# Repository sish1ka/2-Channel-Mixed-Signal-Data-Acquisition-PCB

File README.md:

# 2-Channel-Mixed-Signal-Data-Acquisition-PCB

## Overview

This project involves the design of a 2-channel mixed-signal data acquisition system intended to measure 0–5 V analog signals and convert them into digital data for microcontroller-based processing and analysis.

Each analog input passes through input protection, voltage scaling, buffering, and active low-pass filtering before being sampled by a 12-bit ADC on an STM32 microcontroller.

The system is being designed and simulated using LTspice and will be implemented as a 2-layer PCB using KiCad. In the future, Embedded C will be used for microcontroller data acquisition and MATLAB will be used for data analysis.

## Objectives

* Design a 2-channel analog data acquisition system
* Accept 0–5 V analog input signals
* Scale the input signals to an ADC-compatible voltage range
* Implement input protection against abnormal voltage excursions
* Buffer the analog signals to minimize loading between circuit stages
* Implement 2nd-order active low-pass filtering
* Sample the conditioned signals using a 12-bit ADC
* Transfer acquired data through UART
* Verify circuit behavior through simulation
* Design and verify a 2-layer PCB
* Analyze acquired data using MATLAB

## Tools

* LTspice
* KiCad
* C
* MATLAB
* Git / GitHub

## Circuit Design

## Design Summary

| Parameter                 |                Value |
| ------------------------- | -------------------: |
| Number of channels        |                    2 |
| Input signal              |                0–5 V |
| ADC voltage range         |              0–3.3 V |
| ADC resolution            |               12-bit |
| Sampling rate             |       4 kS/s/channel |
| Useful bandwidth          |             0–100 Hz |
| Low-pass filter           | 2nd-order Sallen-Key |
| Filter cutoff             |              ~297 Hz |
| Nominal system gain       |            ~0.60 V/V |
| Maximum nominal ADC input |               ~3.0 V |
| Microcontroller           |        STM32G031K8T6 |
| Analog op-amp             |              MCP6004 |
| PCB layers                |                    2 |
| PCB dimensions            |          ~80 × 50 mm |
| UART baud rate            |          460800 baud |z

## LTspice Simulation

### Verification Procedure

The analog front end is being verified using a node-by-node transient analysis.

Each verification step checks a specific electrical condition before proceeding to the next stage.

### 1. Voltage divider

**Purpose:**
Verify that the input protection resistor and voltage divider produce the expected scaled voltage for a 0–5 V input signal.

**Circuit Configuration:**

| Component                 |   Value |
| ------------------------- | ------: |
| Input protection resistor |    1 kΩ |
| R_TOP                     | 16.5 kΩ |
| R_BOTTOM                  |   10 kΩ |

**Test Signal:**

```text
SINE(2.5 2.5 10)
```

The input signal has a 2.5 V DC offset, 2.5 V amplitude, and 10 Hz frequency, resulting in a 0–5 V input waveform.

**Transient Analysis:**

```text
.tran 100m
```

The 100 ms simulation window corresponds to one complete cycle of the 10 Hz input signal.

**Procedure:**

1. Apply the 0–5 V test signal to the input.
2. Run a transient analysis for 100 ms in LTspice.
3. Probe the input node.
4. Confirm that the input signal ranges from 0 V to 5 V.
5. Probe the output of the voltage divider.
6. Confirm that the scaled signal ranges from approximately 0 V to 1.82 V.

**Expected Result:**

| Parameter             | Expected |
| --------------------- | -------: |
| Input minimum         |      0 V |
| Input maximum         |      5 V |
| Scaled output minimum |     ~0 V |
| Scaled output maximum |  ~1.82 V |

**Measured Result:**
`Vin = 0–5.00 V`
`Vscaled = 0–1.82 V`

**Result:** Pass

### 2. Diode Voltage Protection Verification

**Purpose:**
Verify that the protection diode limits abnormal negative voltage excursions at the scaled node.

A bipolar test signal is applied to intentionally drive the input below the normal 0–5 V operating range.

**Test Signal:**

```text
SINE(0 5 10)
```

This produces a −5 V to +5 V input waveform.

**Procedure:**

1. Apply the bipolar test signal to the input.
2. Run a transient analysis for 100 ms in LTspice.
3. Probe the scaled node.
4. Observe the negative voltage excursion without the protection diode.
5. Enable the protection diode.
6. Repeat the simulation.
7. Compare the negative voltage excursion with and without the diode.

**Expected Result:**

The protection diode should conduct during the negative voltage excursion and limit the negative voltage at the protected node.

**Measured Result:**
Without the diode, the scaled node follows the negative input excursion. With the diode connected, the negative voltage is clamped and the scaled node no longer follows the negative excursion below the diode's forward-voltage region.

**Result:** Pass

### 3. Buffer Verification

**Purpose:**
Verify that the voltage buffer reproduces the scaled input signal without significantly changing its voltage level. The buffer also isolates the voltage divider from the following filter stage by providing high input impedance and low output impedance.

**Buffer Configuration:**

| Parameter      |                                        Value |
| -------------- | -------------------------------------------: |
| Op-Amp         |                              UniversalOpamp2 |
| Configuration  |                             Voltage follower |
| Supply voltage |                                  3.3 V / 0 V |
| Buffer input   |                       Voltage divider output |
| Buffer output  |                                 Filter input |
| Feedback       | Output directly connected to inverting input |

**Procedure:**

1. Apply the 0–5 V input signal using `SINE(2.5 2.5 10)`.
2. Run the transient simulation for 100 ms.
3. Measure the voltage at the output of the voltage divider.
4. Measure the voltage at the output of the buffer.
5. Compare the two waveforms over the full input cycle.

**Expected Result:**

The buffer output should closely follow the voltage-divider output with approximately unity voltage gain.

$$
A_v = \frac{V_{OUT}}{V_{IN}} \approx 1
$$

For the 0–5 V input signal, the voltage divider produces approximately 0–1.82 V. Therefore, the buffer output should also be approximately 0–1.82 V.

| Measurement           | Expected Result |
| --------------------- | --------------: |
| Buffer input minimum  |            ~0 V |
| Buffer input maximum  |         ~1.82 V |
| Buffer output minimum |            ~0 V |
| Buffer output maximum |         ~1.82 V |
| Voltage gain          |          ~1 V/V |

**Measured Result:**

The buffer output closely follows the voltage-divider output. The buffer input and output waveforms overlap over the 0–1.82 V range, confirming that the voltage follower provides approximately unity gain without significantly altering the signal amplitude.

**Result:** Pass

### 4. Sallen-Key Filter Response Verification

**Purpose:**
Verify that the Sallen-Key stage provides the intended second-order low-pass response, including the expected low-frequency gain, cutoff frequency, and roll-off behavior.

**Filter Configuration:**

| Parameter     |       Value |
| ------------- | ----------: |
| R1            |     5.36 kΩ |
| R2            |     5.36 kΩ |
| C1            |      100 nF |
| C2            |      100 nF |
| Rf            |     5.90 kΩ |
| Rg            |       10 kΩ |
| Op-Amp Supply | 3.3 V / GND |

**Theoretical Low-Pass Cutoff:**

For equal resistor and capacitor values:

$$
f_c = \frac{1}{2\pi RC}
$$

$$
f_c = \frac{1}{2\pi(5.36\,k\Omega)(100\,nF)}
\approx 297\,Hz
$$

The Sallen-Key gain is:

$$
K = 1 + \frac{R_f}{R_g}
$$

$$
K = 1 + \frac{5.90\,k\Omega}{10\,k\Omega}
\approx 1.59
$$

The corresponding low-frequency magnitude is:

$$
20\log_{10}(1.59) \approx 4.03\,dB
$$

For a second-order low-pass filter, the cutoff frequency is approximately **3 dB below the passband magnitude**. Therefore, with a passband magnitude of approximately +4 dB, the expected magnitude at the cutoff is approximately +1 dB.

**Procedure:**

1. Set the LTspice input source to:

   * DC value: `2.5 V`
   * AC amplitude: `1 V`
   * AC phase: `0°`
2. Run an AC sweep using:
   `.ac dec 100 1 100k`
3. Plot the filter transfer function:
   `V(FILTER_OUT)/V(BUF_OUT)`
4. Measure the magnitude in the low-frequency passband.
5. Measure the magnitude near the theoretical cutoff frequency of 297 Hz.
6. Verify the expected attenuation beyond the cutoff region.

**Expected Result:**

| Measurement             |       Expected |
| ----------------------- | -------------: |
| Low-frequency gain      |      ~1.59 V/V |
| Low-frequency magnitude |      ~+4.03 dB |
| Cutoff frequency        |        ~297 Hz |
| Magnitude at cutoff     |      ~+1.03 dB |
| High-frequency roll-off | ~−40 dB/decade |

**Measured Result:**

* At **10 Hz:** approximately **+4 dB**
* At **297 Hz:** approximately **+1 dB**
* The measured response is consistent with the expected second-order low-pass behavior.

**Result:** Pass

The measured passband gain and attenuation at 297 Hz closely match the theoretical response. The filter therefore provides the intended low-pass behavior with a cutoff frequency of approximately 297 Hz.

### 5. ADC Input Range Verification

**Purpose:**
Verify that the conditioned analog signal remains within the STM32 ADC input range and that the complete analog front end provides the intended voltage scaling.

**ADC Configuration:**

| Parameter                    |       Value |
| ---------------------------- | ----------: |
| ADC voltage range            |     0–3.3 V |
| ADC resolution               |      12-bit |
| Input signal                 |       0–5 V |
| ADC input filter             | 47 Ω + 1 nF |
| Expected maximum ADC voltage |      ~3.0 V |

**Procedure:**

1. Connect the Sallen-Key filter output to the ADC input through the 47 Ω series resistor.
2. Add a 1 nF capacitor from the ADC input node to GND.
3. Apply a 0–5 V sinusoidal input using:
   `SINE(2.5 2.5 10)`
4. Run a transient simulation using:
   `.tran 100m`
5. Plot the ADC input node voltage, `V(ADC_IN)`.
6. Verify that the ADC input remains within the 0–3.3 V operating range.

**Expected Result:**

For a 5 V maximum input, the nominal analog gain of approximately 0.60 V/V gives:

$$
V_{ADC,max} \approx 5V \times 0.60
$$

$$
V_{ADC,max} \approx 3.0V
$$

The ADC input should therefore remain below the 3.3 V supply while utilizing most of the available ADC range.

**Measured Result:**

The simulated ADC input waveform remained sinusoidal and reached approximately **2.9 V maximum** for a 5 V maximum input.

| Measurement          | Result |
| -------------------- | -----: |
| Input minimum        |   ~0 V |
| Input maximum        |    5 V |
| ADC minimum          |   ~0 V |
| ADC maximum          | ~2.9 V |
| ADC supply/reference |  3.3 V |

The maximum ADC voltage is approximately 0.4 V below the 3.3 V supply, providing headroom while maintaining a large usable portion of the ADC input range.

**Result:** Pass

The simulated ADC input remains within the 0–3.3 V range and is suitable for connection to the STM32 ADC.

### Results

| Verification                | Theoretical                | Measured                   | Error | Result |
| --------------------------- | -------------------------- | -------------------------- | ----: | ------ |
| Voltage scaling             | 0–1.89 V                   | 0–1.89 V                   |     — | Pass   |
| Negative voltage protection | Negative excursion clamped | Negative excursion clamped |     — | Pass   |
| Buffer                      | Unity gain                 | Unity gain                 |     — | Pass   |
| Filter cutoff               | ~297 Hz                    | ~297 Hz                    |     — | Pass   |
| Complete analog chain       | 0–3.0 V ADC input          | 0–2.9 V ADC input          | ~3.3% | Pass   |

## PCB Design

The PCB was designed in KiCad based on the verified analog front-end and data acquisition circuit.

The board integrates two analog signal-conditioning channels with input protection, voltage scaling, signal conditioning, filtering, and a STM32G031K8Tx microcontroller interface.

### PCB Layout

* **Board size:** 80 × 50 mm
* **Design software:** KiCad
* **Layers:** 2-layer PCB
* **Analog channels:** 2
* **Main controller:** STM32G031K8Tx
* **Analog front-end:** MCP6004 quad op-amp
* **Mounting:** Through-hole and surface-mount components
* **Design verification:** Electrical Rules Check (ERC) and Design Rules Check (DRC)
* **Manufacturing outputs:** Gerber files and drill files generated from the final PCB layout

### Components

| Ref.                   | Component         |         Value | Qty. | Footprint                                                        |
| ---------------------- | ----------------- | ------------: | ---: | ---------------------------------------------------------------- |
| C1, C2, C4, C5, C7, C8 | Ceramic Capacitor |        100 nF |    6 | `Capacitor_SMD:C_0805_2012Metric`                                |
| C3, C6                 | Ceramic Capacitor |          1 nF |    2 | `Capacitor_SMD:C_0805_2012Metric`                                |
| D1, D2                 | Diode             |             — |    2 | `Diode_SMD:D_SOD-123`                                            |
| J1, J2                 | 2-Pin Header      |             — |    2 | `Connector_PinHeader_2.54mm:PinHeader_1x02_P2.54mm_Vertical`     |
| J3                     | 5-Pin Header      |             — |    1 | `Connector_PinHeader_2.54mm:PinHeader_1x05_P2.54mm_Vertical`     |
| J4                     | 4-Pin Header      |             — |    1 | `Connector_PinHeader_2.54mm:PinHeader_1x04_P2.54mm_Vertical`     |
| R1, R7                 | Resistor          |          1 kΩ |    2 | `Resistor_THT:R_Axial_DIN0207_L6.3mm_D2.5mm_P10.16mm_Horizontal` |
| R2, R8                 | Resistor          |     16.455 kΩ |    2 | `Resistor_THT:R_Axial_DIN0207_L6.3mm_D2.5mm_P10.16mm_Horizontal` |
| R3, R9, R13, Rg1, Rg2  | Resistor          |         10 kΩ |    5 | `Resistor_THT:R_Axial_DIN0207_L6.3mm_D2.5mm_P10.16mm_Horizontal` |
| R4, R5, R10, R11       | Resistor          |       5.36 kΩ |    4 | `Resistor_THT:R_Axial_DIN0207_L6.3mm_D2.5mm_P10.16mm_Horizontal` |
| R6, R12                | Resistor          |          47 Ω |    2 | `Resistor_THT:R_Axial_DIN0207_L6.3mm_D2.5mm_P10.16mm_Horizontal` |
| Rf1, Rf2               | Resistor          |        5.9 kΩ |    2 | `Resistor_THT:R_Axial_DIN0207_L6.3mm_D2.5mm_P10.16mm_Horizontal` |
| SW1                    | Push Button       |             — |    1 | `Button_Switch_THT:SW_NKK_GW12LJP`                               |
| U1                     | Quad Op-Amp       |       MCP6004 |    1 | `Package_DIP:DIP-14_W7.62mm`                                     |
| U2                     | Microcontroller   | STM32G031K8Tx |    1 | `Package_QFP:LQFP-32_7x7mm_P0.8mm`                               |

**Total components:** 40

### Connector Pinout

Connector pin assignments are defined in the KiCad schematic.

| Connector | Pins | Function                           |
| --------- | ---: | ---------------------------------- |
| J1        |  1–2 | Channel 1 interface                |
| J2        |  1–2 | Channel 2 interface                |
| J3        |  1–5 | Microcontroller / system interface |
| J4        |  1–4 | Power / system interface           |

> **Note:** Refer to the KiCad schematic for the complete electrical pin assignments and net names.

### Power

The board does not include an onboard voltage regulator. The 3.3 V
rail (STM32 VDD/VDDA, MCP6004 V+) is supplied externally through
**J4 pin 1**, which is expected to be driven directly from a
regulated 3.3 V source — for example, the 3.3 V pin available on
many common USB-to-UART adapters (FTDI FT232RL, CP2102, etc.), or a
bench supply. This was a deliberate simplification to reduce
component count on a first custom board; a future revision could
add an onboard LDO (e.g. AMS1117-3.3) to accept a single unregulated
5 V input instead.

### Circuit Parameters

| Parameter        |                Value |
| ---------------- | -------------------: |
| Supply Voltage   |               +3.3 V |
| Input Range      |                0–5 V |
| ADC Range        |              0–3.3 V |
| Sampling Rate    |       4 kS/s/channel |
| Filter           | 2nd-order Sallen-Key |
| Cutoff Frequency |              ~297 Hz |

### KiCAD schematic

### PCB Layout

### 3D View

### Fabrication Outputs

Gerber and drill files are generated using KiCad for PCB manufacturing.

The fabrication outputs include:

* Front and back copper
* Front and back solder mask
* Silkscreen
* Board outline
* Drill files

The generated files are available in `KiCad/Gerbers/`.

### PCB Design Verification

The PCB layout is checked using KiCad's Design Rules Checker (DRC).

**Target:**

* DRC errors: 0
* Unconnected items: 0
* Board outline: ~80 × 50 mm

## Firmware

**Status:** written and compiles cleanly against the STM32G0 HAL;
not flashed or tested on hardware (see Project Status above).

The firmware implements:

* Clock configuration: HSI16 + PLL → 64 MHz HCLK
* ADC1: 2 channels (PA0/PA1), 12-bit, scan mode
* TIM3: configured to trigger ADC conversions at 4 kHz
* DMA: circular-mode capture into a 256-sample ring buffer
  (128 channel-pairs), with half/full-transfer callbacks
* USART1: 460800 baud, TX via DMA
* A 9-byte binary frame protocol — sync bytes, sequence number,
  CH1/CH2 12-bit ADC codes, and an XOR checksum — for streaming
  samples to a host PC

## MATLAB Data Analysis

**Status:** written and tested (via GNU Octave) using synthetic data
matching the firmware's binary protocol; not yet run against real
captured hardware data.

* `filter_analysis.m` — computes the theoretical Sallen-Key frequency
  response directly from component values and can overlay an
  LTspice AC-sweep export for comparison. Runs standalone, no
  hardware needed.

## Future Work

If this project is picked back up:

1. Fabricate the PCB (JLCPCB/PCBWay, ~80×50mm 2-layer) and obtain an
   ST-Link programmer
2. Flash the firmware and verify each stage in isolation (GPIO →
   ADC polling → timer trigger → DMA → UART), per the staged
   bring-up plan this project was designed around
3. Fill in the DC accuracy, frequency-response, and noise
   measurement tables with real values, and compare against the
   LTspice/theoretical predictions already established
4. Consider adding an onboard 3.3 V LDO so the board accepts a
   single unregulated 5 V input

## Files

* `Documentation/` — design images and verification results
* `KiCad/` — schematic and PCB design files
* `LTspice/` — circuit simulations
* `Firmware/` — STM32 firmware
* `MATLAB/` — data analysis scripts
* `BOM/` — bill of materials
* `Gerbers/` — manufacturing outputs

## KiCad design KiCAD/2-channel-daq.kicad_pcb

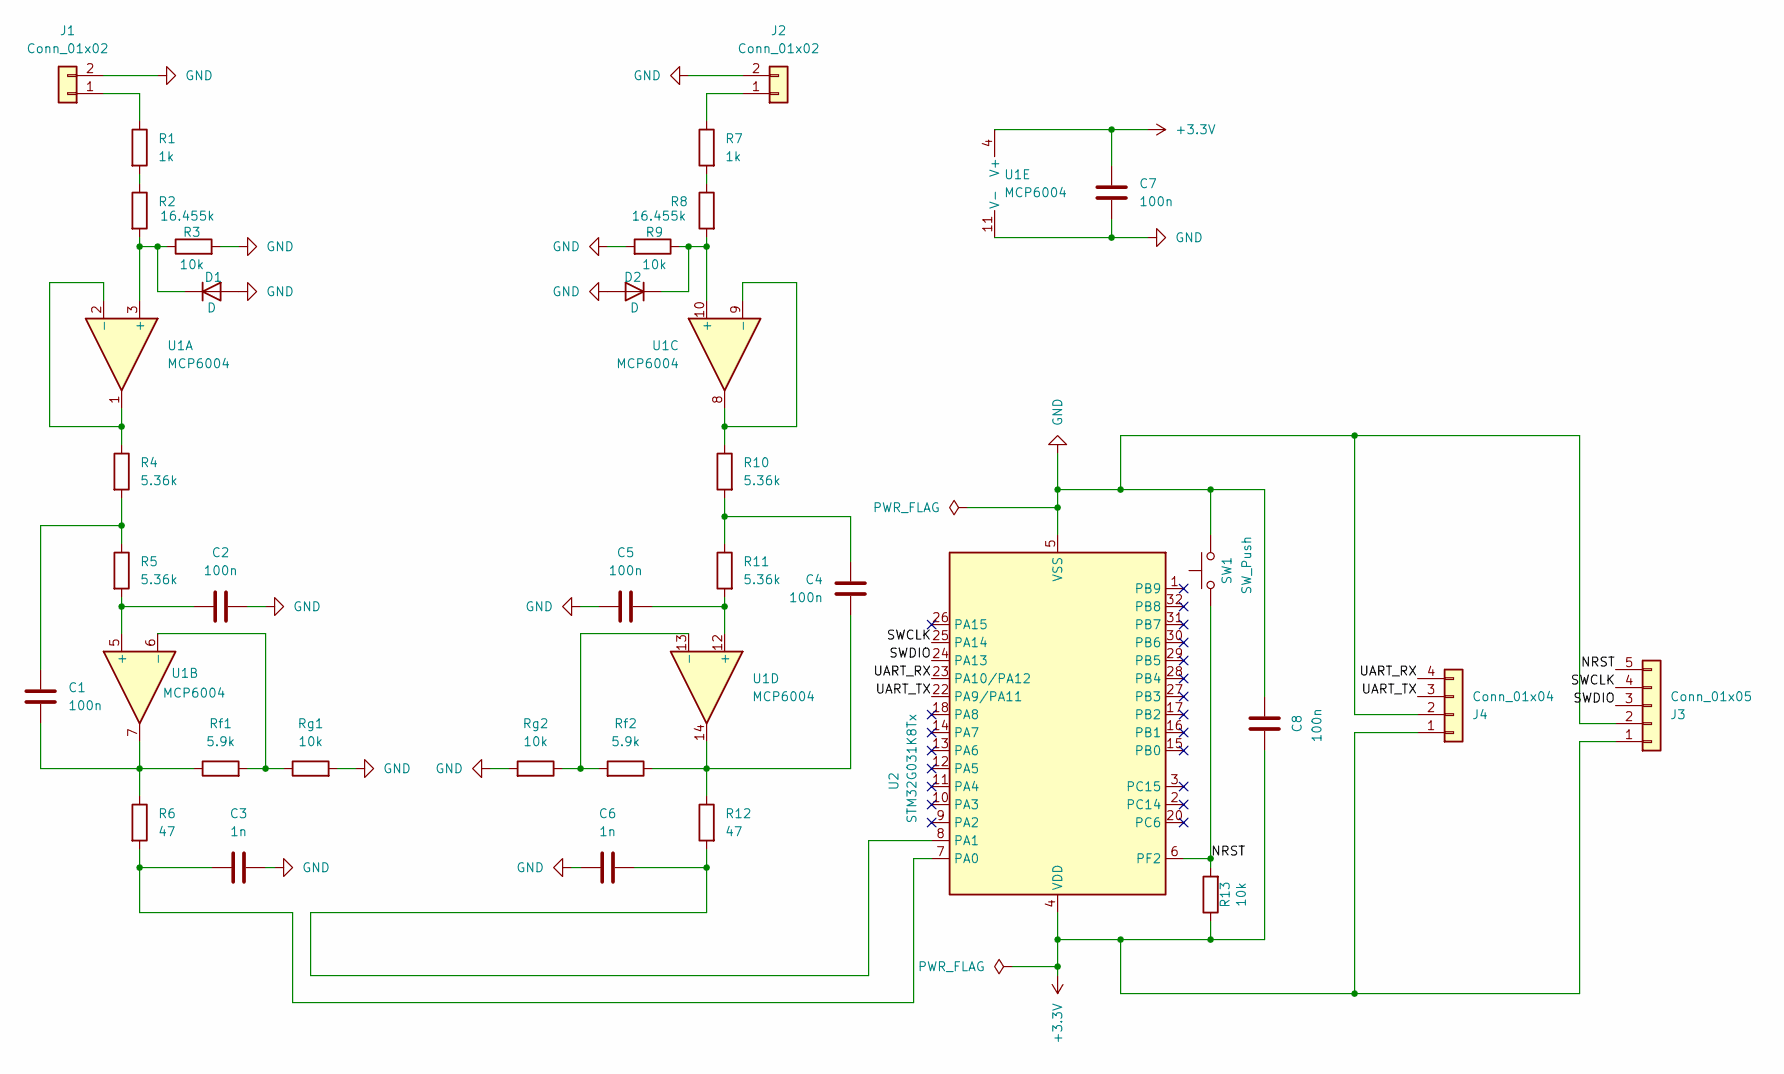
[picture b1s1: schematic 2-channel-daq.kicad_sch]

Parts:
C1, C2, C4, C5, C7, C8: 100n; C_0805_2012Metric
C3, C6: 1n; C_0805_2012Metric
D1, D2: D; D_SOD-123
J1, J2: Conn_01x02; PinHeader_1x02_P2.54mm_Vertical
J3: Conn_01x05; PinHeader_1x05_P2.54mm_Vertical
J4: Conn_01x04; PinHeader_1x04_P2.54mm_Vertical
R1, R7: 1k; R_Axial_DIN0207_L6.3mm_D2.5mm_P10.16mm_Horizontal
R2, R8: 16.455k; R_Axial_DIN0207_L6.3mm_D2.5mm_P10.16mm_Horizontal
R3, R9, R13: 10k; R_Axial_DIN0207_L6.3mm_D2.5mm_P10.16mm_Horizontal
R4, R5, R10, R11: 5.36k; R_Axial_DIN0207_L6.3mm_D2.5mm_P10.16mm_Horizontal
R6, R12: 47; R_Axial_DIN0207_L6.3mm_D2.5mm_P10.16mm_Horizontal
Rf1, Rf2: 5.9k; R_Axial_DIN0207_L6.3mm_D2.5mm_P10.16mm_Horizontal
Rg1, Rg2: 10k; R_Axial_DIN0207_L6.3mm_D2.5mm_P10.16mm_Horizontal
SW1: SW_Push; SW_NKK_GW12LJP
U1: MCP6004; DIP-14_W7.62mm
U2: STM32G031K8Tx; LQFP-32_7x7mm_P0.8mm

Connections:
+3.3V: C7.2, C8.1, J3.1, J4.1, R13.1, U1.4 (V+), U2.4 (VDD)
/NRST: J3.5, R13.2, SW1.1, U2.6 (PF2)
/SWCLK: J3.4, U2.25 (PA14)
/SWDIO: J3.3, U2.24 (PA13)
/UART_RX: J4.4, U2.23 (PA10/PA12)
/UART_TX: J4.3, U2.22 (PA9/PA11)
GND: C2.2, C3.2, C5.2, C6.2, C7.1, C8.2, D1.2 (A), D2.2 (A), J1.2, J2.2, J3.2, J4.2, R3.2, R9.2, Rg1.2, Rg2.2, SW1.2, U1.11 (V-), U2.5 (VSS)
unnamed: C1.1, R4.2, R5.1
unnamed: C1.2, R6.1, Rf1.1, U1.7
unnamed: C4.1, R10.2, R11.1
unnamed: C4.2, R12.1, Rf2.1, U1.14
unnamed: D1.1 (K), R2.2, R3.1, U1.3 (+)
unnamed: D2.1 (K), R8.2, R9.1, U1.10 (+)
unnamed: J1.1, R1.1
unnamed: J2.1, R7.1
unnamed: R1.2, R2.1
unnamed: R7.2, R8.1
unnamed: R4.1, U1.1, U1.2 (-)
unnamed: C2.1, R5.2, U1.5 (+)
unnamed: Rf1.2, Rg1.1, U1.6 (-)
unnamed: R10.1, U1.8, U1.9 (-)
unnamed: C5.1, R11.2, U1.12 (+)
unnamed: Rf2.2, Rg2.1, U1.13 (-)
unnamed: C3.1, R6.2, U2.7 (PA0)
unnamed: C6.1, R12.2, U2.8 (PA1)

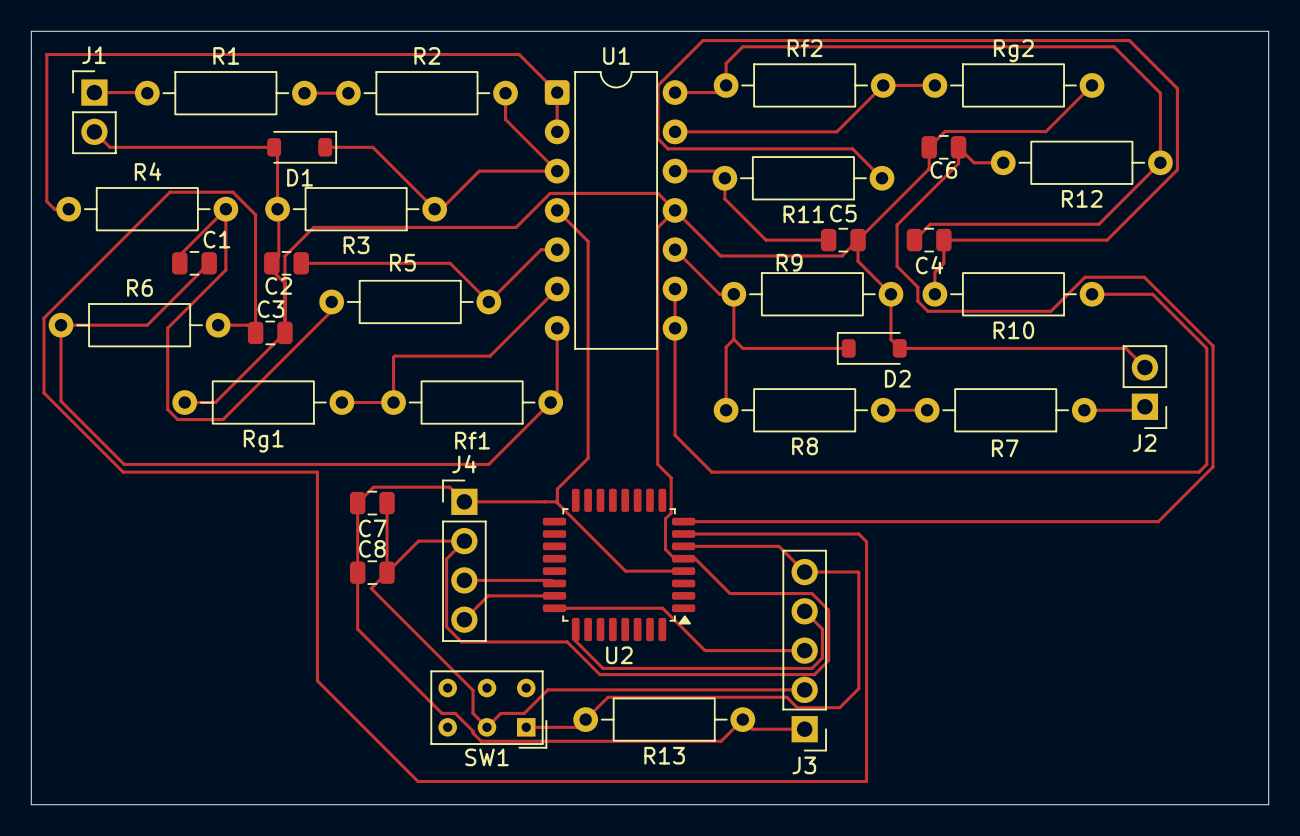
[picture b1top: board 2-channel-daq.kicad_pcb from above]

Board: 2 copper layers, 80.0 x 50.0 mm, 34 parts (0 on the bottom side), 25 nets.

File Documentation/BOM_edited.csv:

## Bill of Materials (BOM)

| Ref.                   | Component         |         Value | Qty. | Footprint                     |
| ---------------------- | ----------------- | ------------: | ---: | ----------------------------- |
| C1, C2, C4, C5, C7, C8 | Ceramic Capacitor |        100 nF |    6 | 0805                          |
| C3, C6                 | Ceramic Capacitor |          1 nF |    2 | 0805                          |
| D1, D2                 | Diode             |             — |    2 | SOD-123                       |
| J1, J2                 | 2-Pin Header      |             — |    2 | 1×02, 2.54 mm                 |
| J3                     | 5-Pin Header      |             — |    1 | 1×05, 2.54 mm                 |
| J4                     | 4-Pin Header      |             — |    1 | 1×04, 2.54 mm                 |
| R1, R7                 | Resistor          |          1 kΩ |    2 | DIN0207, 10.16 mm pitch       |
| R2, R8                 | Resistor          |     16.455 kΩ |    2 | DIN0207, 10.16 mm pitch       |
| R3, R9, R13, Rg1, Rg2  | Resistor          |         10 kΩ |    5 | DIN0207, 10.16 mm pitch       |
| R4, R5, R10, R11       | Resistor          |       5.36 kΩ |    4 | DIN0207, 10.16 mm pitch       |
| R6, R12                | Resistor          |          47 Ω |    2 | DIN0207, 10.16 mm pitch       |
| Rf1, Rf2               | Resistor          |        5.9 kΩ |    2 | DIN0207, 10.16 mm pitch       |
| SW1                    | Push Button       |             — |    1 | NKK GW12LJP                   |
| U1                     | Quad Op-Amp       |       MCP6004 |    1 | DIP-14, 7.62 mm               |
| U2                     | Microcontroller   | STM32G031K8Tx |    1 | LQFP-32, 7×7 mm, 0.8 mm pitch |

**Total components:** 40

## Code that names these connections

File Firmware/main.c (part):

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  * This file assumes the .ioc has been configured with:
  *   - Clock: HSI16 + PLL -> 64 MHz HCLK
  *   - GPIO:  PB3 = GPIO_Output (LED / test toggle)
  *   - ADC1:  IN0 (PA0) + IN1 (PA1), 2 conversions, scan mode,
  *            external trigger = TIM3 TRGO, DMA continuous requests enabled
  *   - TIM3:  Prescaler 0, ARR 15999 (64 MHz / 16000 = 4 kHz), TRGO = Update
  *   - DMA:   ADC1 -> Circular, Half Word, Memory increment enabled
  *   - USART1: PA9 (TX) / PA10 (RX), 460800-8-N-1, TX DMA (Normal mode)
  *
  * NOT hardware-tested. Written and verified to compile against the
  * STM32G0 HAL. See project README for status.
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
/**
  * @brief ADC1 Initialization Function
  *        CH0 (PA0) = Rank 1, CH1 (PA1) = Rank 2
  *        External trigger = TIM3 TRGO, DMA circular, continuous requests.
  * @retval None
  */
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    Error_Handler();
  }

  /* Rank 1: Channel 0 (PA0) — ADC_CH1 */
  sConfig.Channel      = ADC_CHANNEL_0;
  sConfig.Rank         = ADC_REGULAR_RANK_1;
  sConfig.SamplingTime = ADC_SAMPLINGTIME_COMMON_1;
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    Error_Handler();
  }

  /* Rank 2: Channel 1 (PA1) — ADC_CH2 */
  sConfig.Channel      = ADC_CHANNEL_1;
  sConfig.Rank         = ADC_REGULAR_RANK_2;
  sConfig.SamplingTime = ADC_SAMPLINGTIME_COMMON_1;
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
